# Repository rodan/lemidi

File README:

an interface based on a MSP430F5510 that allows the use of usb 1.x-2.0 joysticks 
 with retro gaming PCs that have a game port.

 source:       https://github.com/rodan/lemidi
               https://cadlab.io/projects/lemidi
 author:       Petre Rodan <2b4eda@subdimension.ro>
 license:      GNU GPLv3
 prototype pictures available here: https://photos.app.goo.gl/fXdDBng4dvEepq8V7

 tested and supported joysticks:

    Logitech Extreme 3D Pro
        ID 046d:c215 Logitech, Inc. Extreme 3D Pro

    Logitech Attack 3
        ID 046d:c214 Logitech, Inc. ATK3 (Attack III Joystick)

    Genius F-23
        ID 0458:1004 KYE Systems Corp. (Mouse Systems) Flight2000 F-23 Joystick

 tested game ports:

    Sound Blaster Live! CT-4810
    (any game port should be supported)

 the interface has an inbuilt overcurrent protection that activates if the 
 connected peripheral sinks over 200mA on the 5V bus. once the peripheral is 
 removed service will resume.

LED statuses:

green led - ON  - if peripheral is supported and succesfully initialized
           OFF  - if supported peripheral is disconnected
           OFF  - if overcurrent condition is triggered

red led -   ON  - if init failed or during overcurrent condition
           OFF  - end of init
           OFF  - end of overcurrent condition
   short blink  - during device power-on

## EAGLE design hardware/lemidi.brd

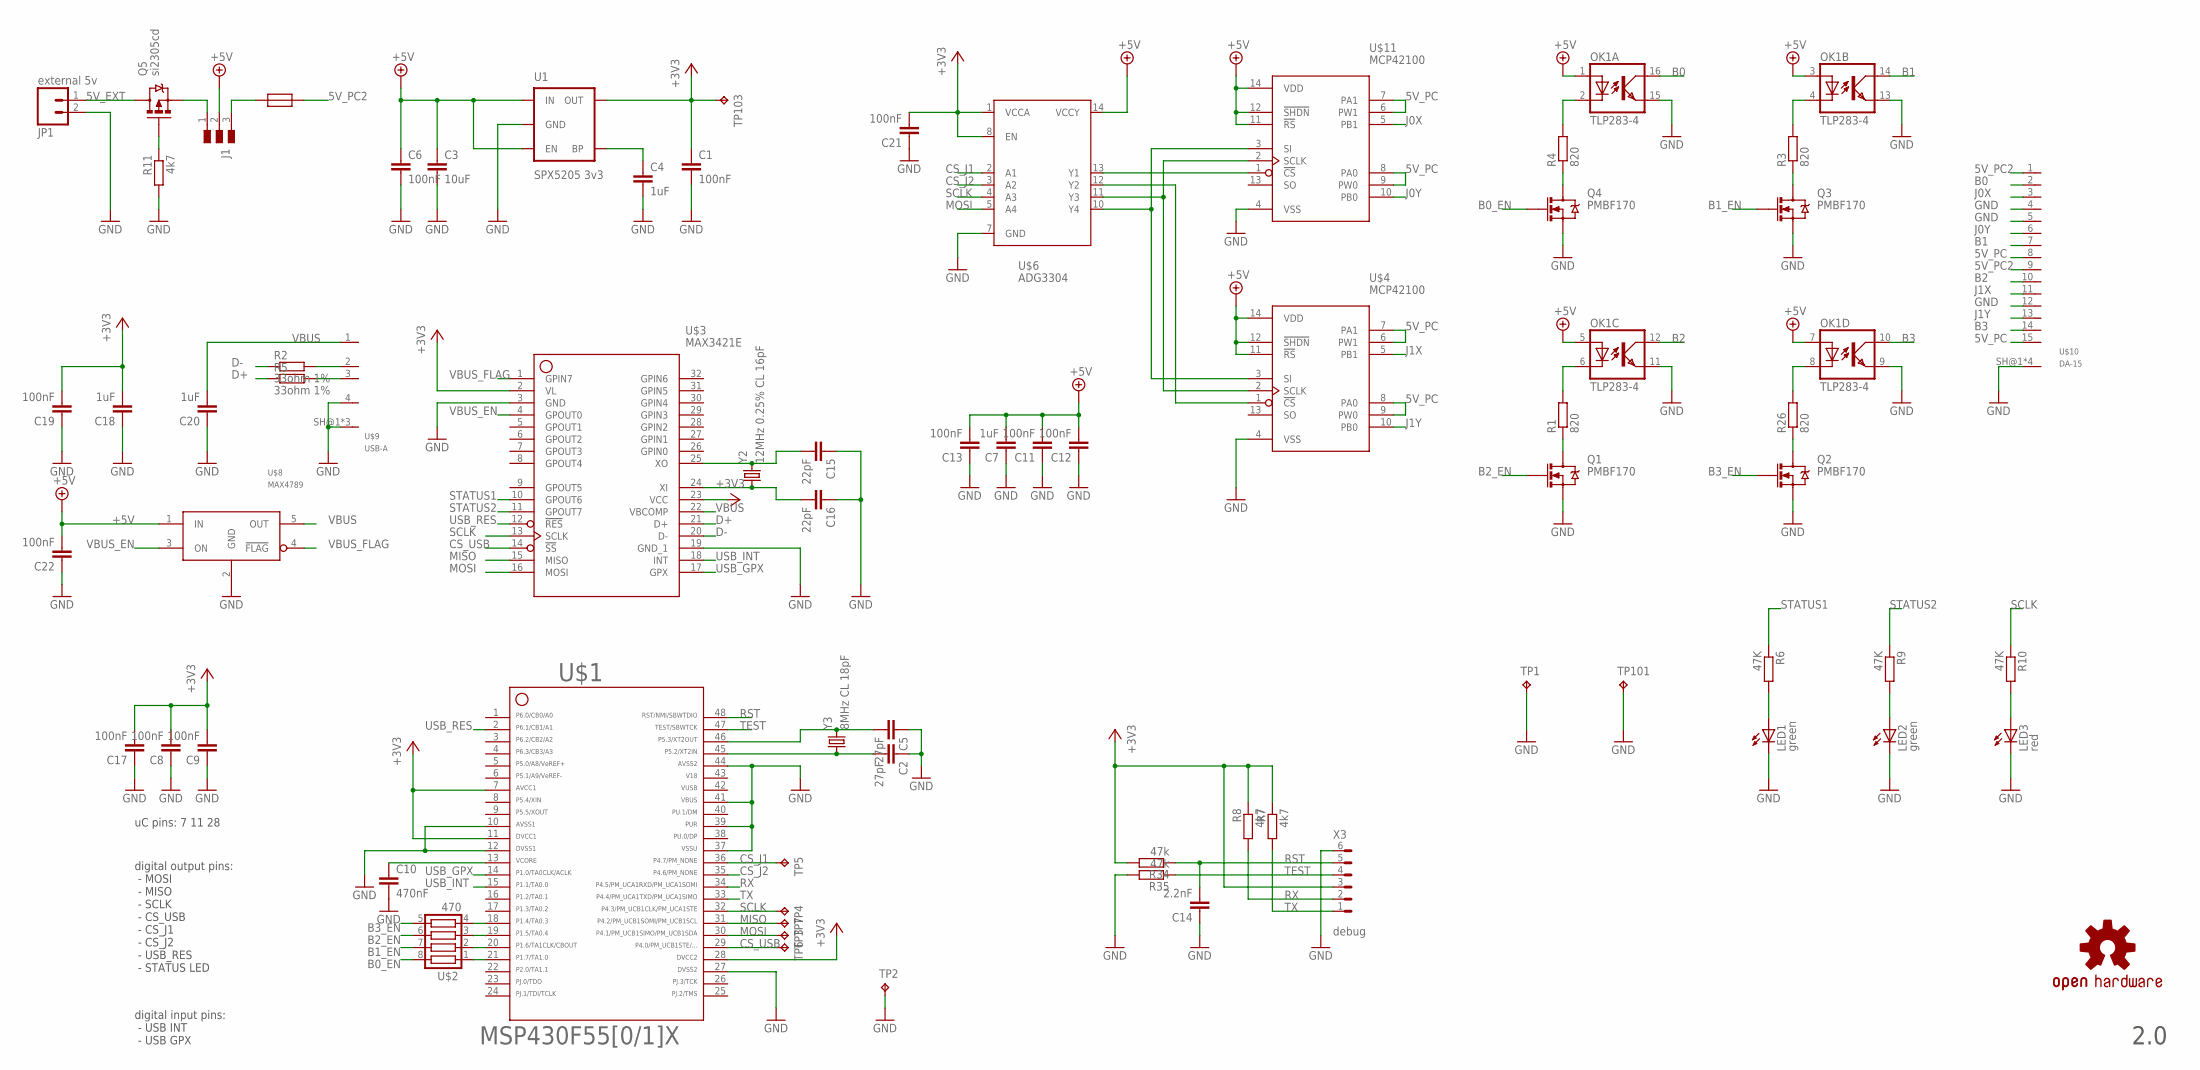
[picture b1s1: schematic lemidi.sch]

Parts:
C1, C6, C8, C9, C11, C12, C13, C17, C19, C21, C22: 100nF; C0805
C2, C5: 27pF; C0805
C3: 10uF; C0805
C4, C7, C18, C20: 1uF; C0805
C10: 470nF; C0805
C14: 2.2nF; C0805
C15, C16: 22pF; C0805
J1: SJ_3P
JP1: external 5v; 1X02
LED1, LED2: green; CHIPLED_0805
LED3: red; CHIPLED_0805
OK1: TLP283-4; MINI-FLAT-16
Q1, Q2, Q3, Q4: PMBF170; SOT23-3
Q5: si2305cd; SOT23-3_POWER
R1, R3, R4, R26: 820; R0805W
R2, R5: 33ohm 1%; R0805W
R6, R9, R10: 47K; R0805W
R7, R8, R11: 4k7; R0805W
R34, R35: 47k; R0805W
TP1, TP2, TP3, TP4, TP5, TP6, TP7, TP101, TP103: TPTP12R; TP12R
U1: SPX5205 3v3; SOT23-5
U$1: MSP430F5510; PT48
U$2: 470; YC164
U$3: MAX3421E; TQFP32
U$4, U$11: MCP42100; SO-14
U$6: ADG3304; TSSOP14
U$7: OSHW-LOGOM; OSHW-LOGO-M
U$8: MAX4789; SOT23-5
U$9: USB-A; UBA-4R-D14T-4D
U$10: DA-15; ADAM_TECH_D-SUB_15
U$12: RESETTABLE_1210; 1210
X3: debug; 0530480610
Y2: 12MHz 0.25% CL 16pF; CRYSTAL-SMD-11.4X4.35
Y3: 8MHz CL 18pF; CRYSTAL-SMD-11.4X4.35

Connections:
5V_EXT: JP1.1, Q5.3 (D)
5V_PC: U$4.6 (PW1), U$4.7 (PA1), U$4.8 (PA0), U$4.9 (PW0), U$10.8, U$10.15, U$11.6 (PW1), U$11.7 (PA1), U$11.8 (PA0), U$11.9 (PW0)
5V_PC2: U$10.1, U$10.9, U$12.P$2
12MHX_XI: C16.2, U$3.24 (XI), Y2.1
12MHZ_XO: C15.2, U$3.25 (XO), Y2.2
42: U$1.42
43: U$1.43
+3V3: C1.1, C8.2, C9.2, C17.2, C18.2, C19.2, C21.2, R7.1, R8.1, R34.2, TP103.TP, U1.5 (OUT), U$1.7, U$1.11, U$1.28, U$3.2 (VL), U$3.23 (VCC), U$6.1 (VCCA), U$6.8 (EN), X3.3 (4)
+5V: C3.1, C6.1, C7.2, C11.2, C12.2, C13.2, C22.2, J1.2, OK1.1 (A), OK1.3 (A), OK1.5 (A), OK1.7 (A), U1.1 (IN), U1.3 (EN), U$4.11 (!RS), U$4.12 (!SHDN), U$4.14 (VDD), U$6.14 (VCCY), U$8.1 (IN), U$11.11 (!RS), U$11.12 (!SHDN), U$11.14 (VDD)
B0: OK1.16 (COL), U$10.2
B0_EN: Q4.1 (G), U$2.8
B1: OK1.14 (COL), U$10.7
B1_EN: Q3.1 (G), U$2.7
B2: OK1.12 (COL), U$10.10
B2_EN: Q1.1 (G), U$2.6
B3: OK1.10 (COL), U$10.14
B3_EN: Q2.1 (G), U$2.5
CS_J1: TP5.TP, U$1.36, U$6.2 (A1)
CS_J2: U$1.35, U$6.3 (A2)
CS_USB: TP6.TP, U$1.29, U$3.14 (!SS)
D+: R5.1, U$3.21 (D+)
D-: R2.1, U$3.20 (D-)
GND: C1.2, C2.1, C3.2, C4.2, C5.1, C6.2, C7.1, C8.1, C9.1, C10.2, C11.1, C12.1, C13.1, C14.1, C15.1, C16.1, C17.1, C18.1, C19.1, C20.1, C21.1, C22.1, JP1.2, LED1.C, LED2.C, LED3.C, OK1.9 (EMIT), OK1.11 (EMIT), OK1.13 (EMIT), OK1.15 (EMIT), Q1.2 (S), Q2.2 (S), Q3.2 (S), Q4.2 (S), R11.2, R35.2, TP1.TP, TP2.TP, TP101.TP, U1.2 (GND), U$1.10, U$1.12, U$1.27, U$1.37, U$1.39, U$1.41, U$1.44, U$3.3 (GND), U$3.19 (GND_1), U$4.4 (VSS), U$6.7 (GND), U$8.2 (GND), U$9.4, U$9.SH@1 (SH), U$9.SH@2 (SH), U$9.SH@3 (SH), U$10.4, U$10.5, U$10.12, U$10.SH@1 (SHIELD), U$10.SH@2 (SHIELD), U$10.SH@3 (SHIELD), U$10.SH@4 (SHIELD), U$11.4 (VSS), X3.6 (1)
HIGH_CS1: U$6.13 (Y1), U$11.1 (!CS)
HIGH_CS2: U$4.1 (!CS), U$6.12 (Y2)
HIGH_MOSI: U$4.3 (SI), U$6.10 (Y4), U$11.3 (SI)
HIGH_SCLK: U$4.2 (SCLK), U$6.11 (Y3), U$11.2 (SCLK)
J0X: U$10.3, U$11.5 (PB1)
J0Y: U$10.6, U$11.10 (PB0)
J1X: U$4.5 (PB1), U$10.11
J1Y: U$4.10 (PB0), U$10.13
MISO: TP7.TP, U$1.31, U$3.15 (MISO)
MOSI: TP3.TP, U$1.30, U$3.16 (MOSI), U$6.5 (A4)
unnamed: LED1.A, R6.2
unnamed: C4.1, U1.4 (BP)
unnamed: U$1.18, U$2.4
unnamed: LED2.A, R9.2
unnamed: Q1.3 (D), R1.1
unnamed: C10.1, U$1.13
unnamed: OK1.6 (C), R1.2
unnamed: U$1.19, U$2.3
unnamed: OK1.8 (C), R26.2
unnamed: J1.3, U$12.P$1
unnamed: LED3.A, R10.2
unnamed: Q3.3 (D), R3.1
unnamed: OK1.4 (C), R3.2
unnamed: Q4.3 (D), R4.1
unnamed: OK1.2 (C), R4.2
unnamed: R5.2, U$9.3
unnamed: R2.2, U$9.2
unnamed: U$1.20, U$2.2
unnamed: U$1.21, U$2.1
unnamed: Q2.3 (D), R26.1
unnamed: J1.1, Q5.2 (S)
unnamed: Q5.1 (G), R11.1
RST: C14.2, R34.1, U$1.48, X3.5 (2)
RX: R8.2, U$1.34, X3.2 (5)
SCLK: R10.1, TP4.TP, U$1.32, U$3.13 (SCLK), U$6.4 (A3)
STATUS1: R6.1, U$3.10 (GPOUT6)
STATUS2: R9.1, U$3.11 (GPOUT7)
TEST: R35.1, U$1.47, X3.4 (3)
TX: R7.2, U$1.33, X3.1 (6)
USB_GPX: U$1.14, U$3.17 (GPX)
USB_INT: U$1.15, U$3.18 (INT)
USB_RES: U$1.2, U$3.12 (!RES)
VBUS: C20.2, U$3.22 (VBCOMP), U$8.5 (OUT), U$9.1
VBUS_EN: U$3.4 (GPOUT0), U$8.3 (ON)
VBUS_FLAG: U$3.1 (GPIN7), U$8.4 (!FLAG)
XT2IN: C2.2, U$1.45, Y3.1
XT2OUT: C5.2, U$1.46, Y3.2

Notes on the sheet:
2.0
uC pins: 7 11 28
digital output pins: - MOSI - MISO - SCLK - CS_USB - CS_J1 - CS_J2 - USB_RES - STATUS LED
digital input pins: - USB INT - USB GPX

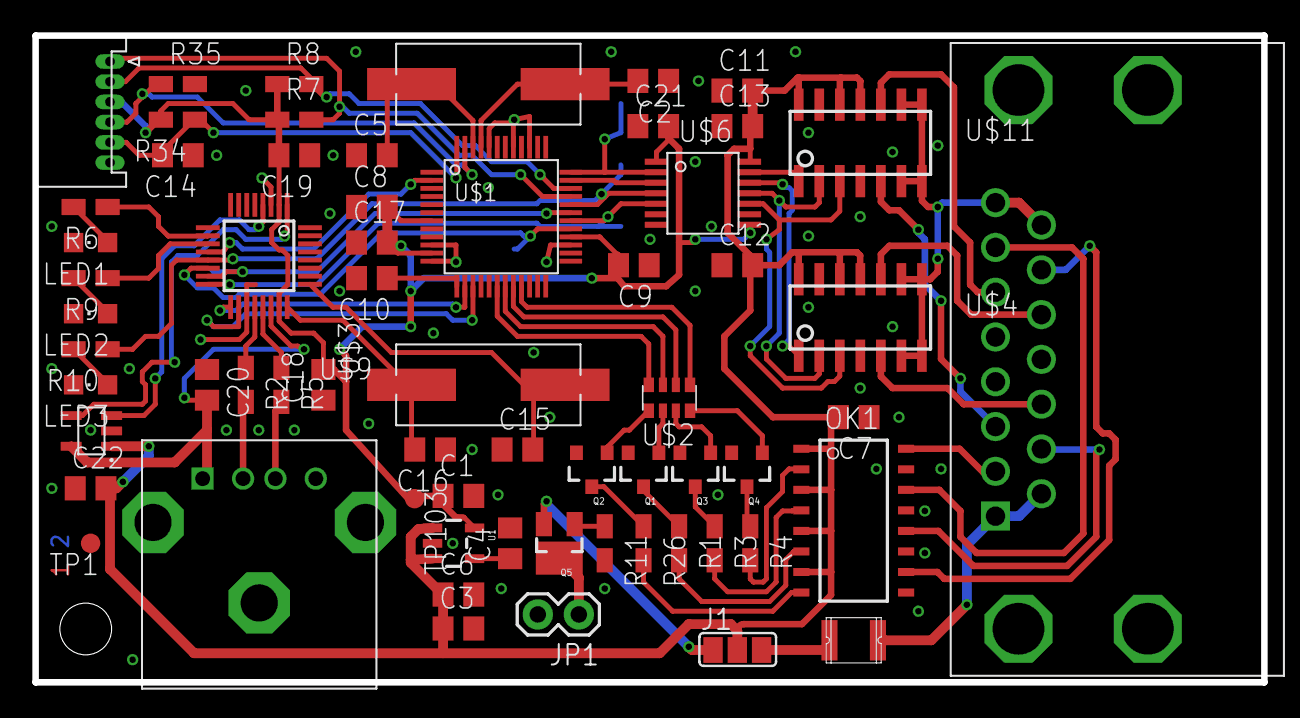
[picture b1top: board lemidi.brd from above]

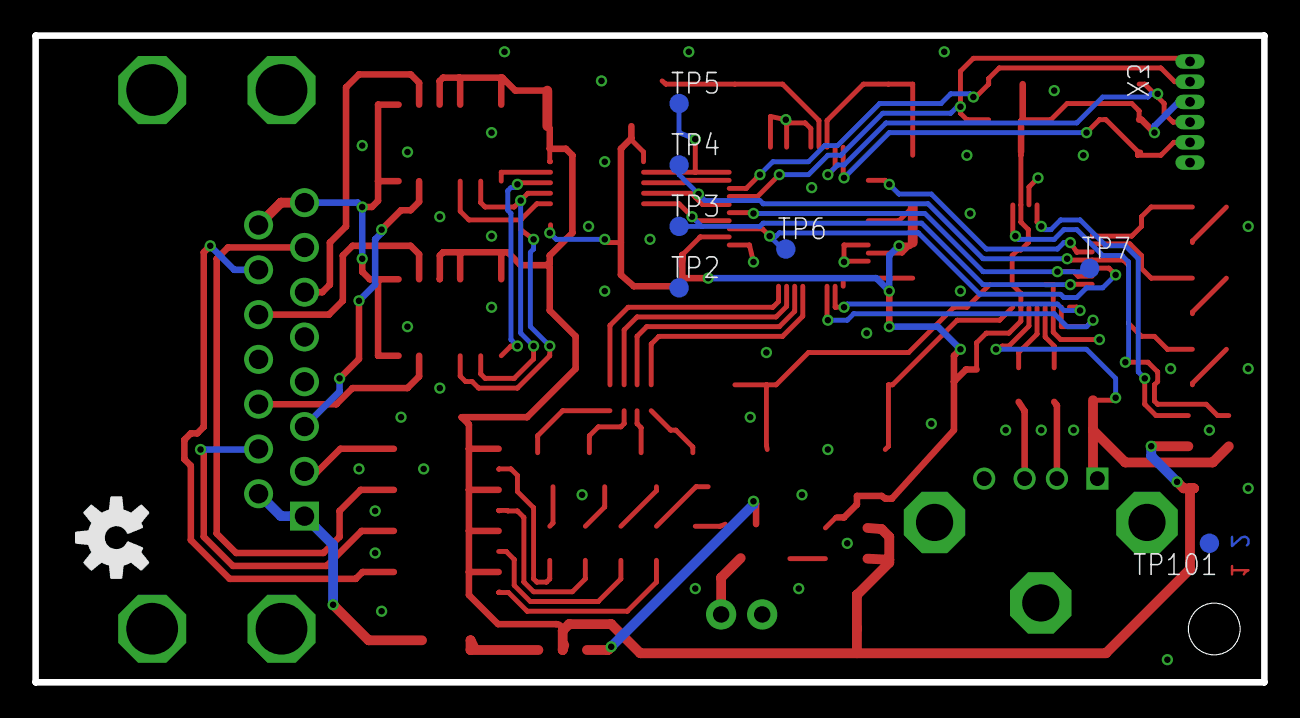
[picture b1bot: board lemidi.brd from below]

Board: 2 copper layers, 76.0 x 40.0 mm, 71 parts (8 on the bottom side), 68 nets.

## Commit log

2018-12-18 Deleted README.md
2018-12-18 latest
2018-12-19 new URLs for sources
2018-12-31 happy new year
2019-01-02 ERC pass
2019-01-02 DRC pass
2019-01-02 1st cleanup
2019-01-02 2nd cleanup
2019-01-02 3rd cleanup
2019-01-02 split 5v inputs from the midi connector, add fuse, add reverse polarity protection for external 5v input
2019-01-05 max5415
2019-01-05 switch to MCP42xxx digital pot
2019-01-07 testing
2019-01-24 rev 2
2019-01-26 assembly done
2019-01-27 read, write MAX3421 registers
2019-01-28 proper usb init
2019-01-30 interrupt handlers
2019-01-31 try merge with UHS3.0
2019-02-01 fix LPM3
2019-02-01 sys_messagebus enum -> uint types
2019-02-03 added cpp code, none working
2019-02-07 cleanup
2019-02-07 base timer0 on SMCLK
2019-02-07 switch to 115200 baud
2019-02-07 add usb_spec header
2019-02-07 ignore GERBER files
2019-02-08 GET_DEVICE_DESCRIPTOR in config
2019-02-09 address-related functions added
2019-02-09 debug print cleanu
2019-02-11 replace CONFIG_PRINTF with CONFIG_LOG_LEVEL
2019-02-13 add LUFA lib files
2019-02-16 support for Genius F-23
2019-02-16 indent
2019-02-16 add traces
2019-02-17 peripheral not ready during busprobe()
2019-02-17 rename file
2019-02-17 switch to 2MHz SPI bus
2019-02-18 speed issues
2019-02-19 testing logitech extreme 3d
2019-02-19 enable watchdog
2019-02-20 add FLAG define
2019-02-20 add overcurrent protection
2019-02-21 save less HID items
2019-02-21 compatibility with CCS - part1
2019-02-21 compatibility with CCS - part2
2019-02-21 compatibility with CCS - part3
2019-02-21 compatibility with CCS - part4
2019-02-21 compatibility with CCS - part5
2019-02-21 RAM usage optimization
2019-02-22 readme update
2021-06-14 typo

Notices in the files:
parts and their libraries:
SparkFun-Connectors: Licensing: Creative Commons ShareAlike 4.0 International - https://creativecommons.org/licenses/by-sa/4.0
